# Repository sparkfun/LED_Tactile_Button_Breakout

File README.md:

LED Tactile Button Breakout
===========================
[ 
*LED Tactile Button Breakout (BOB-10467)*](https://www.sparkfun.com/products/10467)

This is a breakout board for tactile LED buttons. 

Repository Contents
-------------------
* **/Hardware** - All Eagle design files (.brd, .sch)

License Information
-------------------
The hardware is released under [Creative Commons Share-alike 3.0](http://creativecommons.org/licenses/by-sa/3.0/).

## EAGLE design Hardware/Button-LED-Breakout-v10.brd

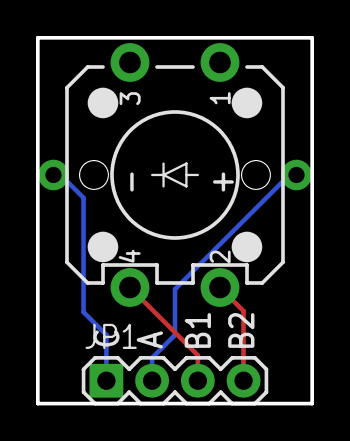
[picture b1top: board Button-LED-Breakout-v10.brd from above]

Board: 2 copper layers, 15.2 x 20.3 mm, 4 parts (1 on the bottom side), 4 nets.

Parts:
JP1: 1X04
JP3: LOGO-SFESK; SFE-LOGO-FLAME
S1: Switch; TACTILE-PTH-LED-12MM
U$1: CREATIVE_COMMONS

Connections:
unnamed: JP1.4, S1.2
unnamed: JP1.3, S1.4
unnamed: JP1.2, S1.A
unnamed: JP1.1, S1.C

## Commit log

2014-01-23 Adding hardware files
2014-01-23 Update README.md
    Adding product information and descriptions.
2025-06-30 Update README.md
    Updating link

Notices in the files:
parts and their libraries:
SparkFun: Released under the Creative Commons Attribution Share-Alike 3.0 License
